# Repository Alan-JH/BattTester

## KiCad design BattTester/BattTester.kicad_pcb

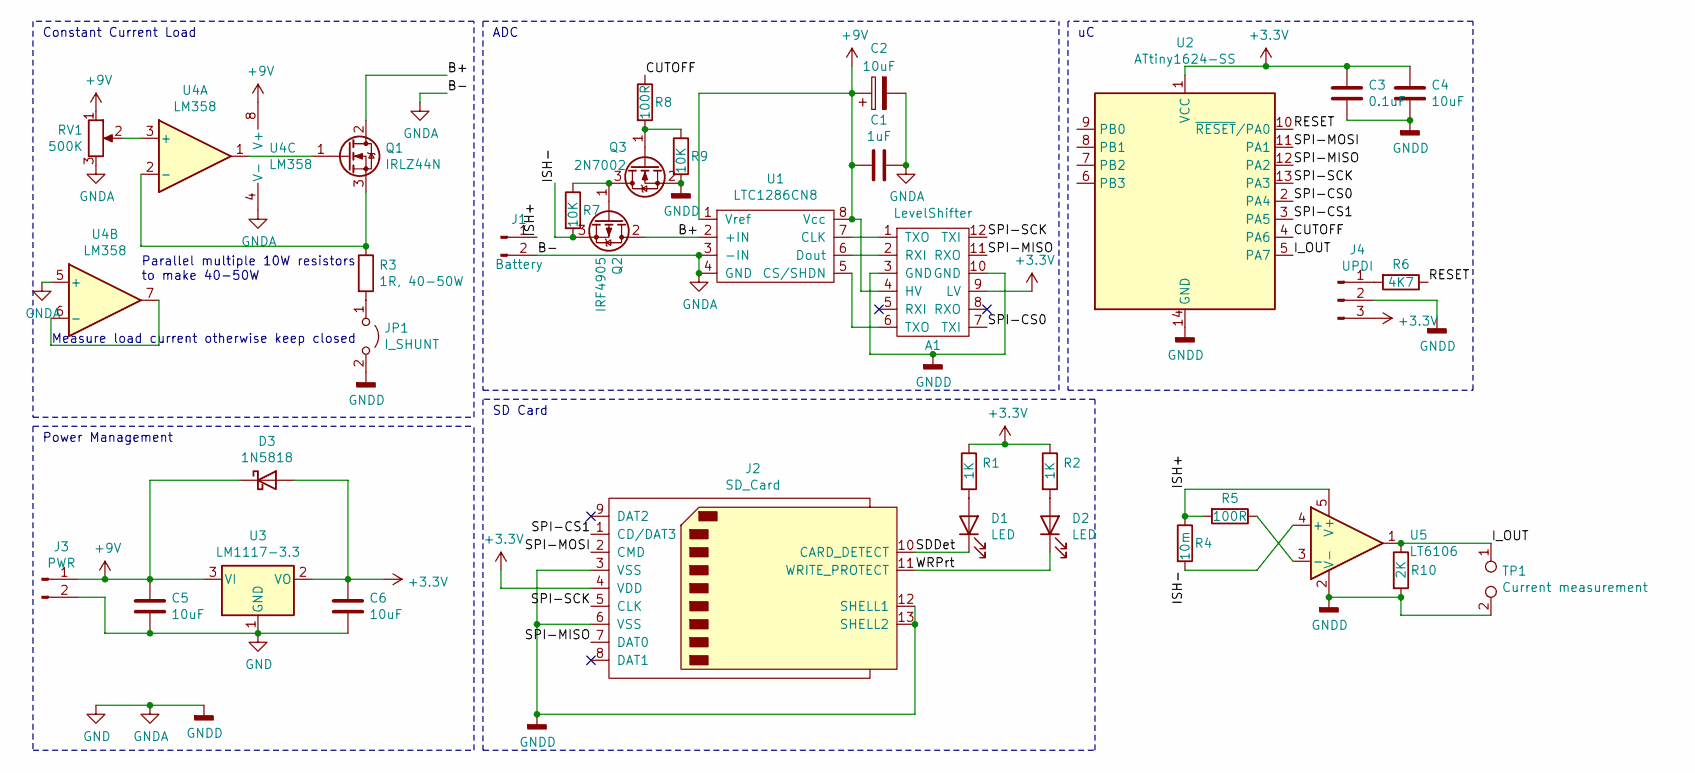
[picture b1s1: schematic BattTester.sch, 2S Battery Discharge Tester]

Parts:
A1: LevelShifter; LevelShifterBreakout
C1: 1uF; C_0805_2012Metric_Pad1.18x1.45mm_HandSolder
C2: 10uF; C_1206_3216Metric_Pad1.33x1.80mm_HandSolder
C3: 0.1uF; C_0805_2012Metric_Pad1.18x1.45mm_HandSolder
C4, C5, C6: 10uF; C_0805_2012Metric_Pad1.18x1.45mm_HandSolder
D1, D2: LED; LED_0805_2012Metric_Pad1.15x1.40mm_HandSolder
D3: 1N5818; D_DO-15_P10.16mm_Horizontal
J1: Battery; PinHeader_1x02_P2.54mm_Vertical
J2: SD_Card; SD_TE_2041021
J3: PWR; PinHeader_1x02_P2.54mm_Vertical
J4: UPDI; PinHeader_1x03_P2.54mm_Vertical
JP1: I_SHUNT; PinHeader_1x02_P2.54mm_Vertical
Q1: IRLZ44N; TO-220-3_Vertical
Q2: IRF4905; TO-220-3_Vertical
Q3: 2N7002; SOT-23
R1, R2: 1K; R_1206_3216Metric_Pad1.30x1.75mm_HandSolder
R3: 1R, 40-50W; 10xParallel_R_Axial_DIN0614_L14.3mm_D5.7mm_P15.24mm_Horizon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
R4: 10m; R_2816_7142Metric_Pad3.20x4.45mm_HandSolder
R5: 100R; R_0805_2012Metric_Pad1.20x1.40mm_HandSolder
R6: 4K7; R_1206_3216Metric_Pad1.30x1.75mm_HandSolder
R7, R9: 10K; R_1206_3216Metric_Pad1.30x1.75mm_HandSolder
R8: 100R; R_1206_3216Metric_Pad1.30x1.75mm_HandSolder
R10: 2K; R_0805_2012Metric_Pad1.20x1.40mm_HandSolder
RV1: 500K; PinHeader_1x03_P2.54mm_Vertical
TP1: Current measurement; PinHeader_1x02_P2.54mm_Vertical
U1: LTC1286CN8; DIP-8_W7.62mm_Socket
U2: ATtiny1624-SS; SOIC-14_3.9x8.7mm_P1.27mm
U3: LM1117-3.3; TO-220-3_Vertical
U4: LM358; DIP-8_W7.62mm_Socket
U5: LT6106; SOT-23-5

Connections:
+3V3: A1.9 (LV), C3.1, C4.1, C6.1, D3.2 (A), J2.4 (VDD), J4.3, R1.1, R2.1, U2.1 (VCC), U3.2 (VO)
+9V: A1.4 (HV), C1.2, C2.1, C5.1, D3.1 (K), J3.1, RV1.1, U1.1 (Vref), U1.8 (Vcc), U3.3 (VI), U4.8 (V+)
/B+: Q1.2 (D), Q2.2 (D), U1.2 (+IN)
/CUTOFF: R8.1, U2.4 (PA6)
/ISH+: J1.1, R4.1, R5.2, U5.5 (V+)
/ISH-: Q2.3 (S), R4.2, R7.2, U5.4 (+)
/I_OUT: R10.1, TP1.1, U2.5 (PA7), U5.1
/RESET: R6.1, U2.10 (~RESET~/PA0)
/SDDet: D1.1 (K), J2.10 (CARD_DETECT)
/SPI-CS0: A1.7 (TXI), U2.2 (PA4)
/SPI-CS1: J2.1 (CD/DAT3), U2.3 (PA5)
/SPI-MISO: A1.11 (RXO), J2.7 (DAT0), U2.12 (PA2)
/SPI-MOSI: J2.2 (CMD), U2.11 (PA1)
/SPI-SCK: A1.12 (TXI), J2.5 (CLK), U2.13 (PA3)
/WRPrt: D2.1 (K), J2.11 (WRITE_PROTECT)
GND: A1.3 (GND), A1.10 (GND), C1.1, C2.2, C3.2, C4.2, C5.2, C6.2, J1.2, J2.3 (VSS), J2.6 (VSS), J2.12 (SHELL1), J2.13 (SHELL2), J3.2, J4.2, JP1.2 (B), Q3.2 (S), R9.2, R10.2, RV1.3, TP1.2, U1.3 (-IN), U1.4 (GND), U2.14 (GND), U3.1 (GND), U4.4 (V-), U4.5 (+), U5.2 (V-)
unnamed: A1.1 (TXO), U1.7 (CLK)
unnamed: A1.2 (RXI), U1.6 (Dout)
unnamed: A1.6 (TXO), U1.5 (CS/SHDN)
unnamed: D1.2 (A), R1.2
unnamed: D2.2 (A), R2.2
unnamed: J4.1, R6.2
unnamed: JP1.1 (A), R3.2
unnamed: Q1.1 (G), U4.1
unnamed: Q1.3 (S), R3.1, U4.2 (-)
unnamed: Q2.1 (G), Q3.3 (D), R7.1
unnamed: Q3.1 (G), R8.2, R9.1
unnamed: R5.1, U5.3 (-)
unnamed: RV1.2, U4.3 (+)
unnamed: U4.6 (-), U4.7

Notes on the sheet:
Measure load current otherwise keep closed
Power Management
Constant Current Load
ADC
SD Card
Parallel multiple 10W resistors to make 40-50W

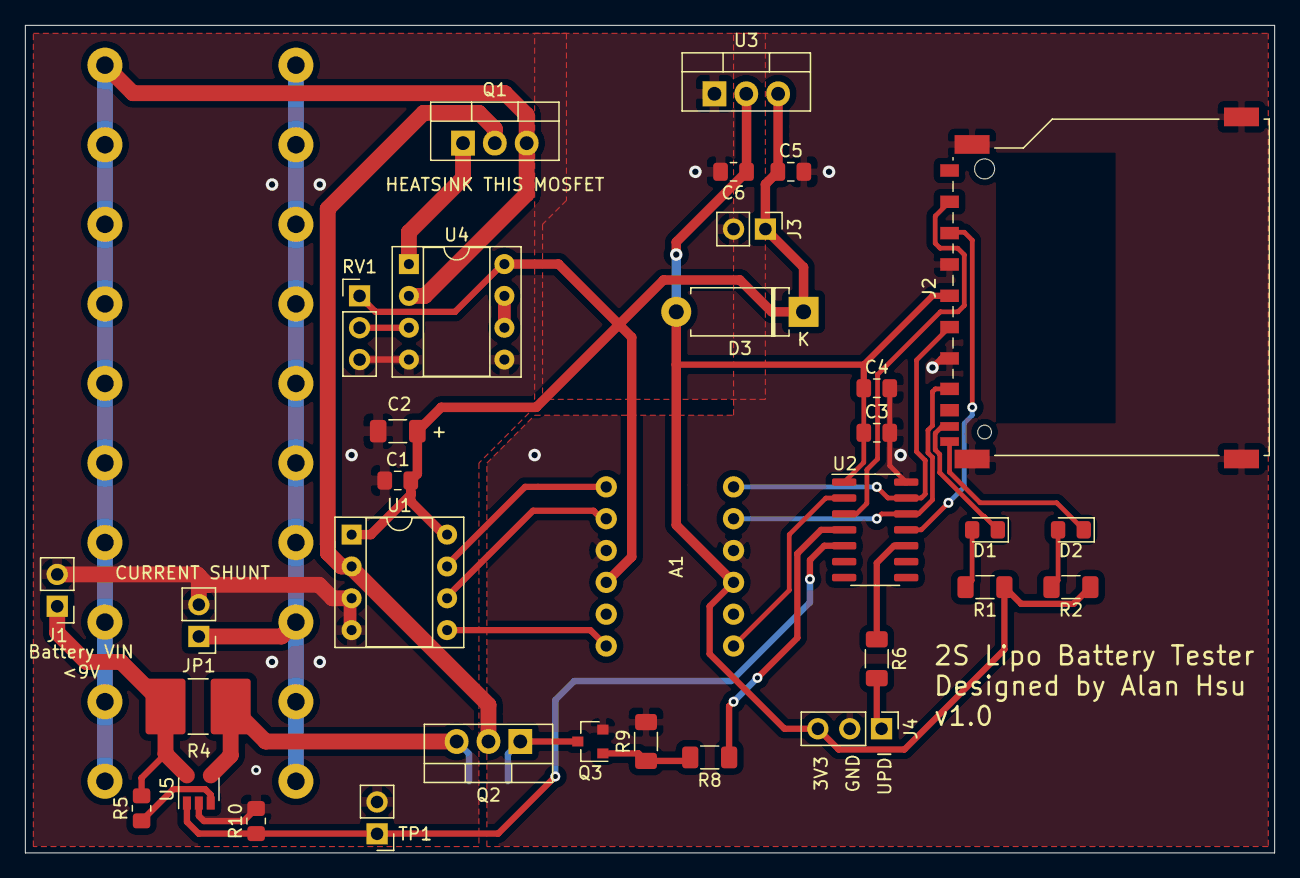
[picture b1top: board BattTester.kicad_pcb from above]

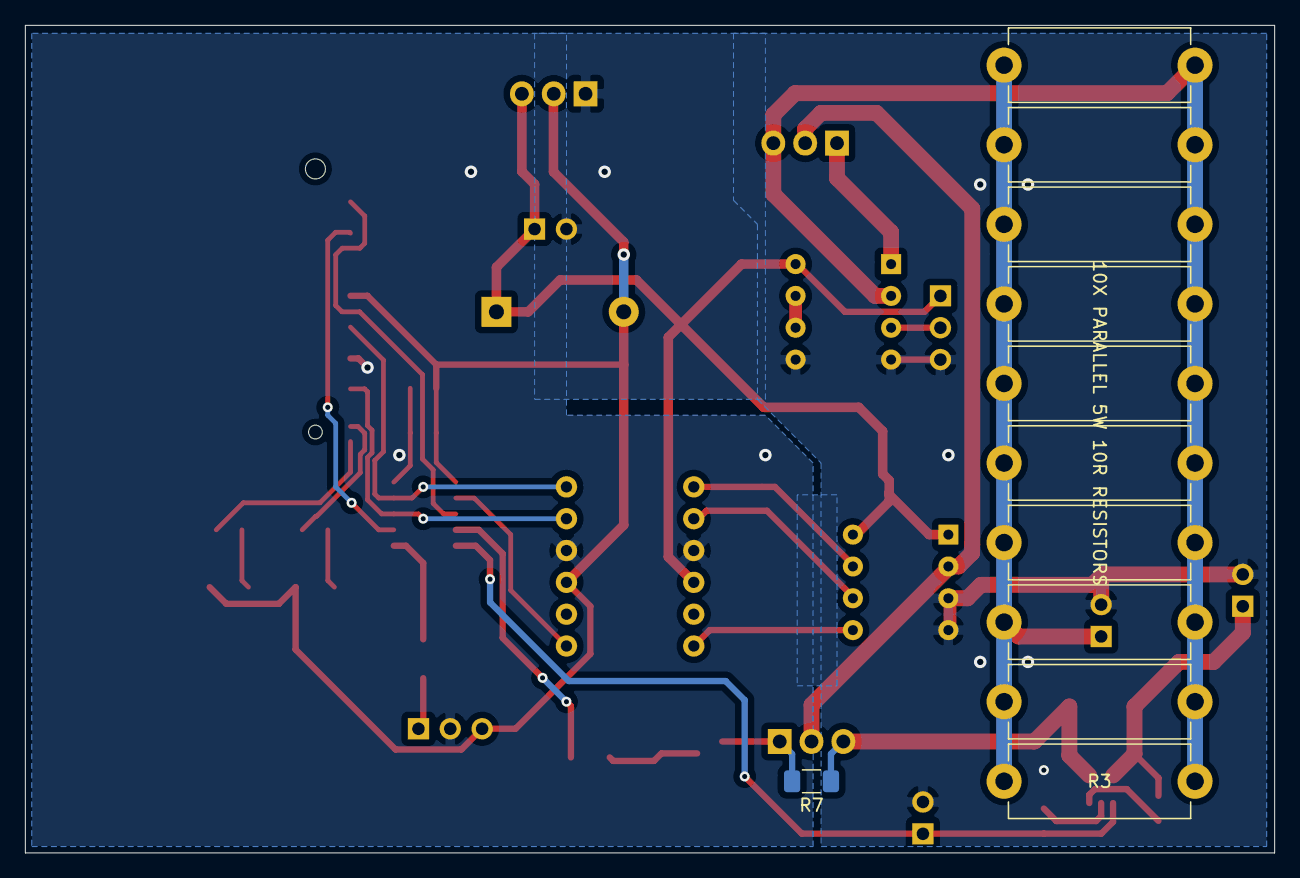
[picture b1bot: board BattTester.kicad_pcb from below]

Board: 2 copper layers, 99.7 x 66.0 mm, 35 parts (2 on the bottom side), 30 nets.

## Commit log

2021-10-17 Constant current load
2021-10-17 level shifter placeholder
2021-10-17 Clean up schematic, add level shifter breakout
2021-10-17 grounding
2021-10-18 Finish routing
2021-10-18 minor name fix
2021-10-18 fix paths
2021-10-18 fix updi header
2021-10-18 minor sch edit
2021-10-18 cutoff mosfet and higher power Rload
2021-10-18 silkscreen update
2021-10-19 work on things
2021-11-13 Fix #1
2021-11-14 start on firmware, export gerbers
2021-11-17 update gerbers, finish firmware
2021-11-18 current check
2021-11-19 add current sense
2021-11-19 add current measurement
2021-11-24 finished routing
2021-11-24 add test point
2021-11-26 standardize dip-8, tie off second lm358 output
